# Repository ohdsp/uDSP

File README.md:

# [Open Hardware DSP Platform](www.ohdsp.org)
## uDSP 1.1
### A 5cm x 5cm DSP board using Analog Device SigmaDSP devices
### Supports ADAU1466, ADAU1462, ADAU1452, ADAU1451, ADAU1450
### Selfboot and external control supported
### All I/O routed out
---
# README
### Disclaimer
Copyright Paul Janicki 2019

Licensed under the TAPR Open Hardware License (www.tapr.org/OHL)

This documentation is distributed WITHOUT ANY EXPRESS OR IMPLIED WARRANTY, INCLUDING OF MERCHANTABILITY, SATISFACTORY QUALITY AND FITNESS FOR A PARTICULAR PURPOSE.

### Changelog
1.1:
Add CS1 and CS2 to SPI header - removed 3V3 power
Add 3V3 monitor option to reset circuit

### What is this repository for?

**Quick summary**

This is a simple self-bootable DSP board with 4 I2S input and 4 I2S output connectors. When used with the ADAU146x, ADAU1451 and ADAU1452 parts there are also optical input and output connectors for off-board mounted connectors. 

There is an SPI connector for connection to the Analog Devices SigmaStudio USBi to EZ-Board Adapter (ADZS-USBI2EZB) or equivalent. 

The board also features master and slave SPI connectors for use with other boards. 

The board has space for a self-boot EEPROM. When used with the ADZS-USBI2EZB or compatible device the board can be programmed to selfboot with the last program written. The board can also be controlled using an external mircocontroller.

This board forms part the of the open hardware DSP platform which is designed to be a highly customisable and flexible DSP platform. 

This repository contains the KiCad design files, manufacturing Gerber/drill files, and PDF/drawing files for this board.

### What is the project folder structure?
Most folder names are self explanatory. Starting from the top level:
*uDSP*
+ *Bill of Materials*  - This contains the bill of materials in CVS, LibreOffice Calc and XML formats
+ *Drawings* - This contains PDF and SVG Schematic and PCB files
+ *Gerbers* - This contains the PCB Gerbers and drill drawings for manufacture, there is also a zip file ready to send to most manufacturers
+ *KiCad* - This contains the original KiCad schematic and PCB design files

### How do I get set up?

**Summary of set up**

1. Set your self up a directory on a local disk, something simple will make life easier (eg C:\Electronics on Windows as used here), but anywhere will do just fine.
2. Download the Kicad-Libs from [https://github.com/ohdsp/KiCad-Libs](https://github.com/ohdsp/KiCad-Libs) and place in C:\Electronics\Kicad-Libs (or your chosen folder) 
3. Create a OHDSP subdirectory in C:\Electronics (so C:\Electronics\OHDSP)
3. Download this project to C:\Electronics\OHDSP\uDSP
4. Fire up Kicad
5. Open the main project file C:\Electronics\OHDSP\uDSP\KiCad\uDSP.pro
7. Do as you wish with the project, just keep it under the TAPR Open Hardware License.
Note: For library issues see below.

Make sure your git setup doesn't exclude files used in the project (like .LIB files) or things may go wrong down the line.

**KiCad Library Configuration**

Note that libraries are setup using relative paths, if you follow the above instructions things should work just fine. Below is the default library setup.

To setup eeschema component libraries:
From KiCad main window go to menu Tools -> Edit Schematic Symbols. In the new Window go to menu Preferences -> Manage Symbol Libraries.

On the new "Symbol Libraries" window select the "Project Specific Libraries" tab. The "Append Library" and "Remove Library" buttons can be used to add/remove enteries.
The standard setup is:

|   | Active | Nickname        | Library Path                                        | Plugin Type | Options | Description |
|---|--------|-----------------|-----------------------------------------------------|-------------|---------|-------------|
| 1 | Ticked | power           | ${KICAD_SYMBOL_DIR}/power.lib                       | Legacy      | (blank) | (blank)     |
| 2 | Ticked | MyKiCadLibs-Lib | ${KIPRJMOD}/../../../KiCad-Libs/MyKiCadLibs-Lib.lib | Legacy      | (blank) | (blank)     |

${KICAD_SYMBOL_DIR}  is set under the Enviromnet Variable Configuration. Close Symbol Libraries dialogue and go "Preferences" -> "Configure Paths..."

${KICAD_SYMBOL_DIR} is set to C:\Program Files\KiCad\share\kicad\library - this is the default for a KiCad install on the C drive

${KIPRJMOD} is automatically set to the location of the project (.pro file), in this example this would be C:\Electronics\OHDSP\uDSP\KiCad

To setup Pcbnew libraries:
From KiCad main window go to menu Tools -> Edit PCB Footprints. In the new Window go to menu Preferences -> Manage Symbol Libraries.

On the new "Symbol Libraries" window select the "Project Specific Libraries" tab. The "Append Library" and "Remove Library" buttons can be used to add/remove enteries.
The standard setup is:

|   | Active | Nickname               | Library Path                                                  | Plugin Type | Options | Description |
|---|--------|------------------------|---------------------------------------------------------------|-------------|---------|-------------|
| 1 | Ticked | MyKiCadLibs-Footprints | ${KIPRJMOD}/../../../KiCad-Libs/MyKiCadLibs-Footprints.pretty | KiCad       | (blank) | (blank)     |

${KIPRJMOD} is automatically set to the location of the project (.pro file), in this example this would be C:\Electronics\OHDSP\uDSP\KiCad

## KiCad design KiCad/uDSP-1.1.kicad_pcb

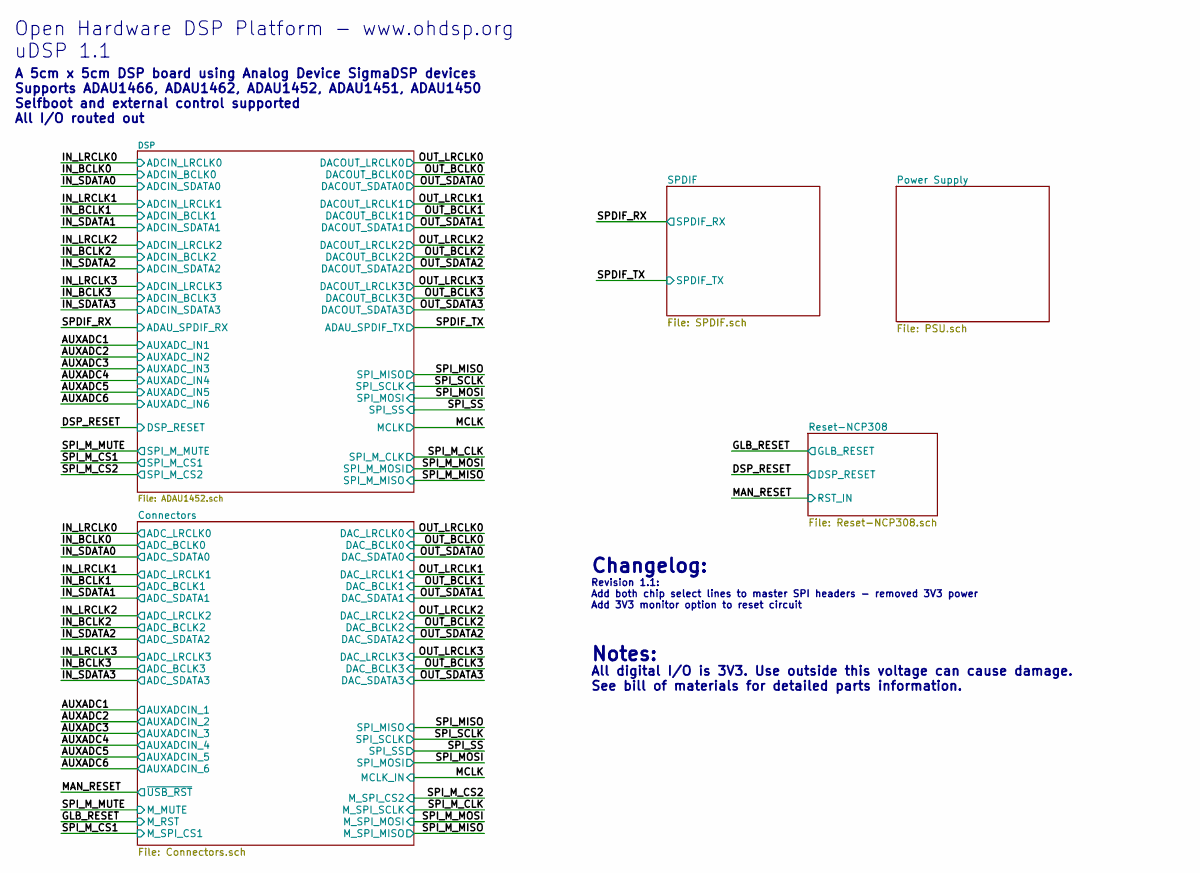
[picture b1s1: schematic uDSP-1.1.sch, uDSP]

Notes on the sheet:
All digital I/O is 3V3. Use outside this voltage can cause damage. See bill of materials for detailed parts information.
Notes:
A 5cm x 5cm DSP board using Analog Device SigmaDSP devices Supports ADAU1466, ADAU1462, ADAU1452, ADAU1451, ADAU1450 Selfboot and external control supported All I/O routed out
Open Hardware DSP Platform - www.ohdsp.org uDSP 1.1
Changelog:
Revision 1.1: Add both chip select lines to master SPI headers - removed 3V3 power Add 3V3 monitor option to reset circuit

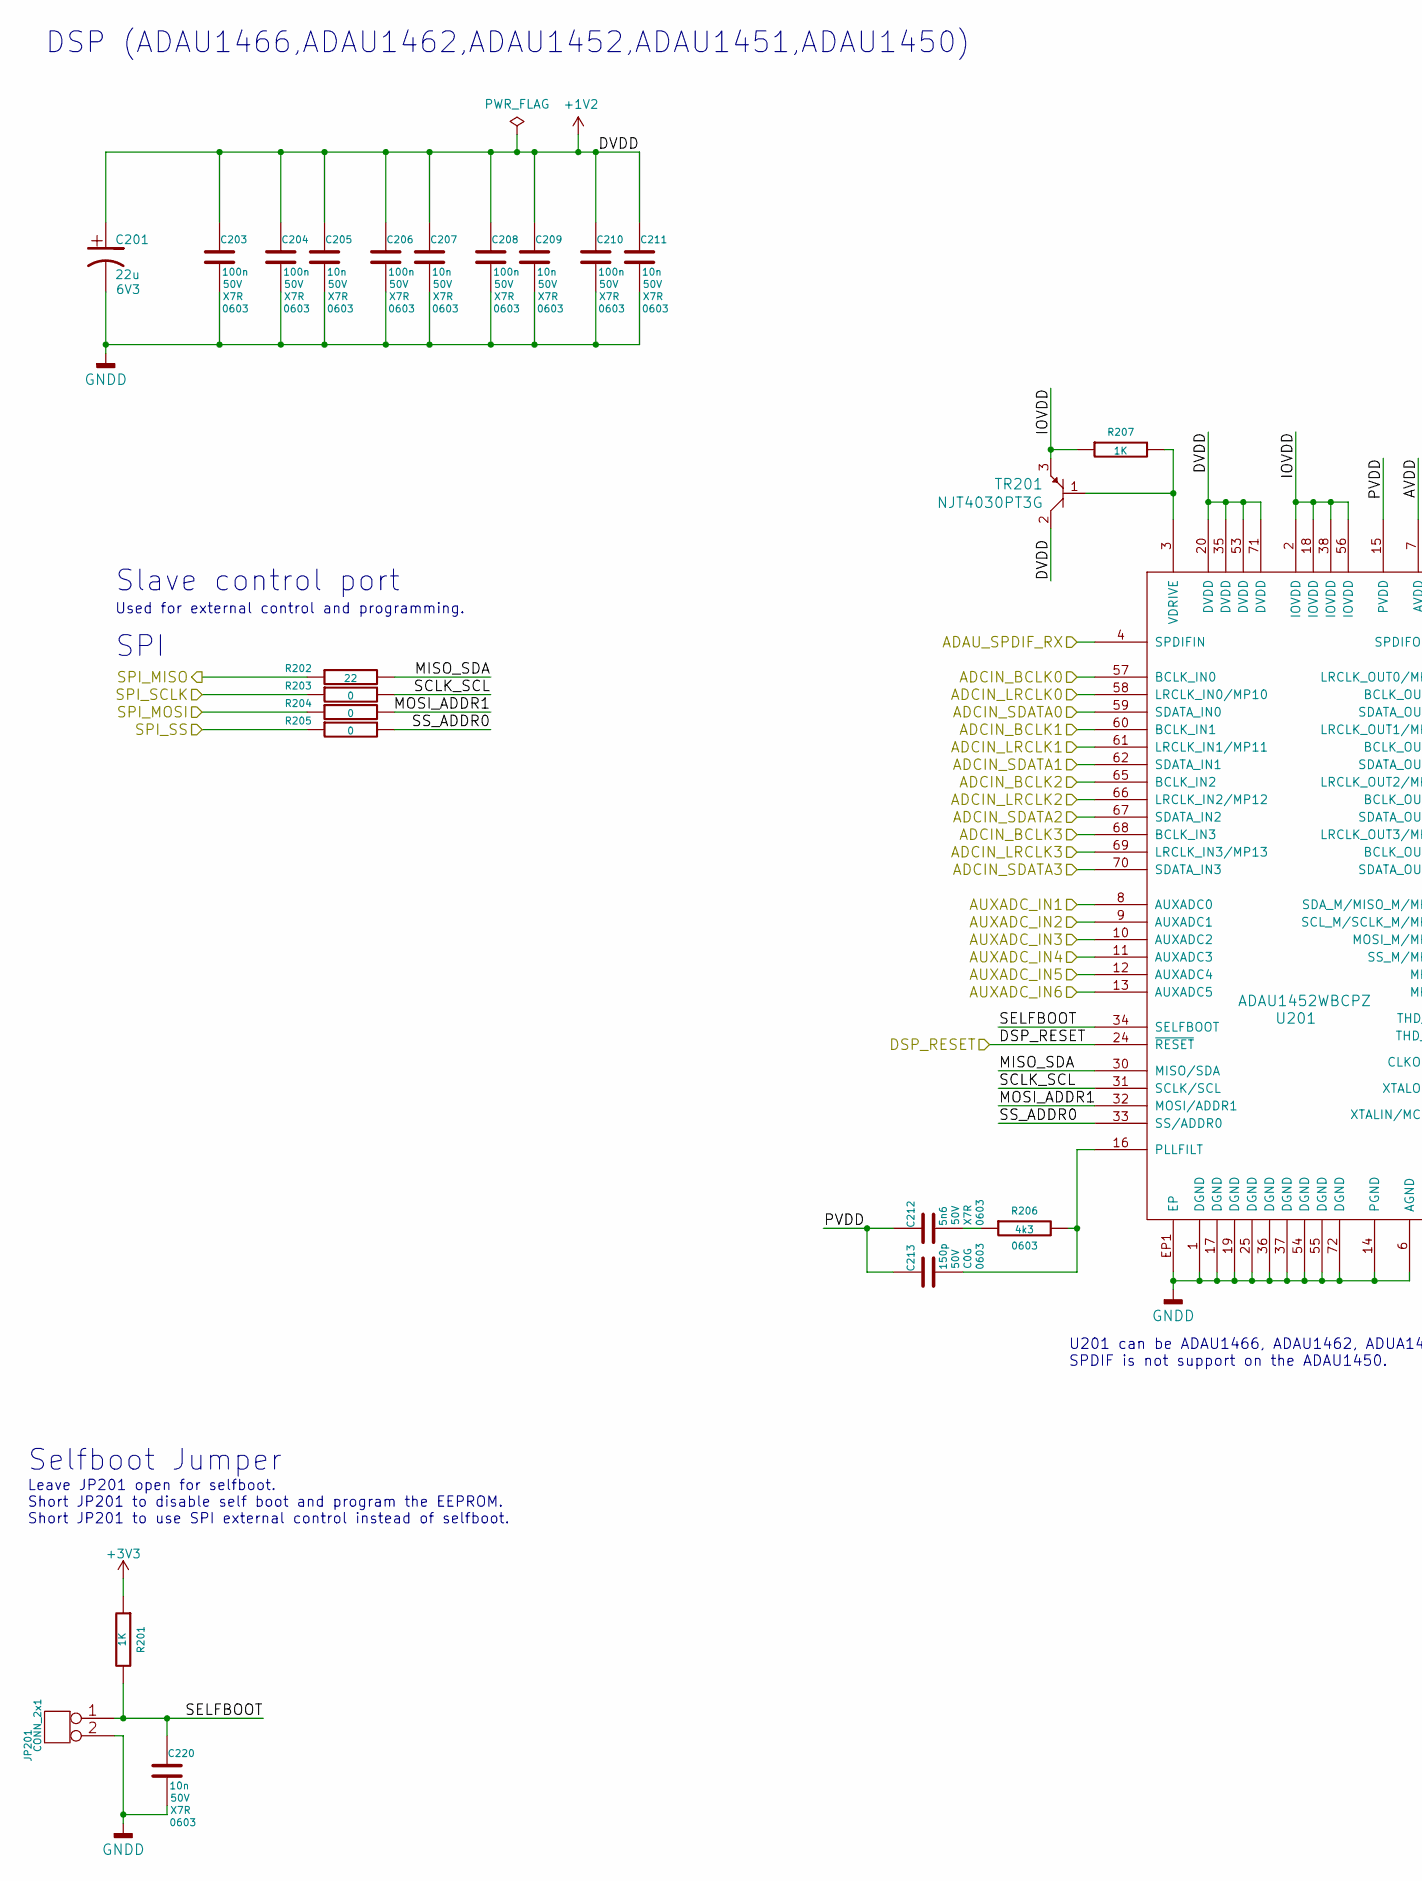
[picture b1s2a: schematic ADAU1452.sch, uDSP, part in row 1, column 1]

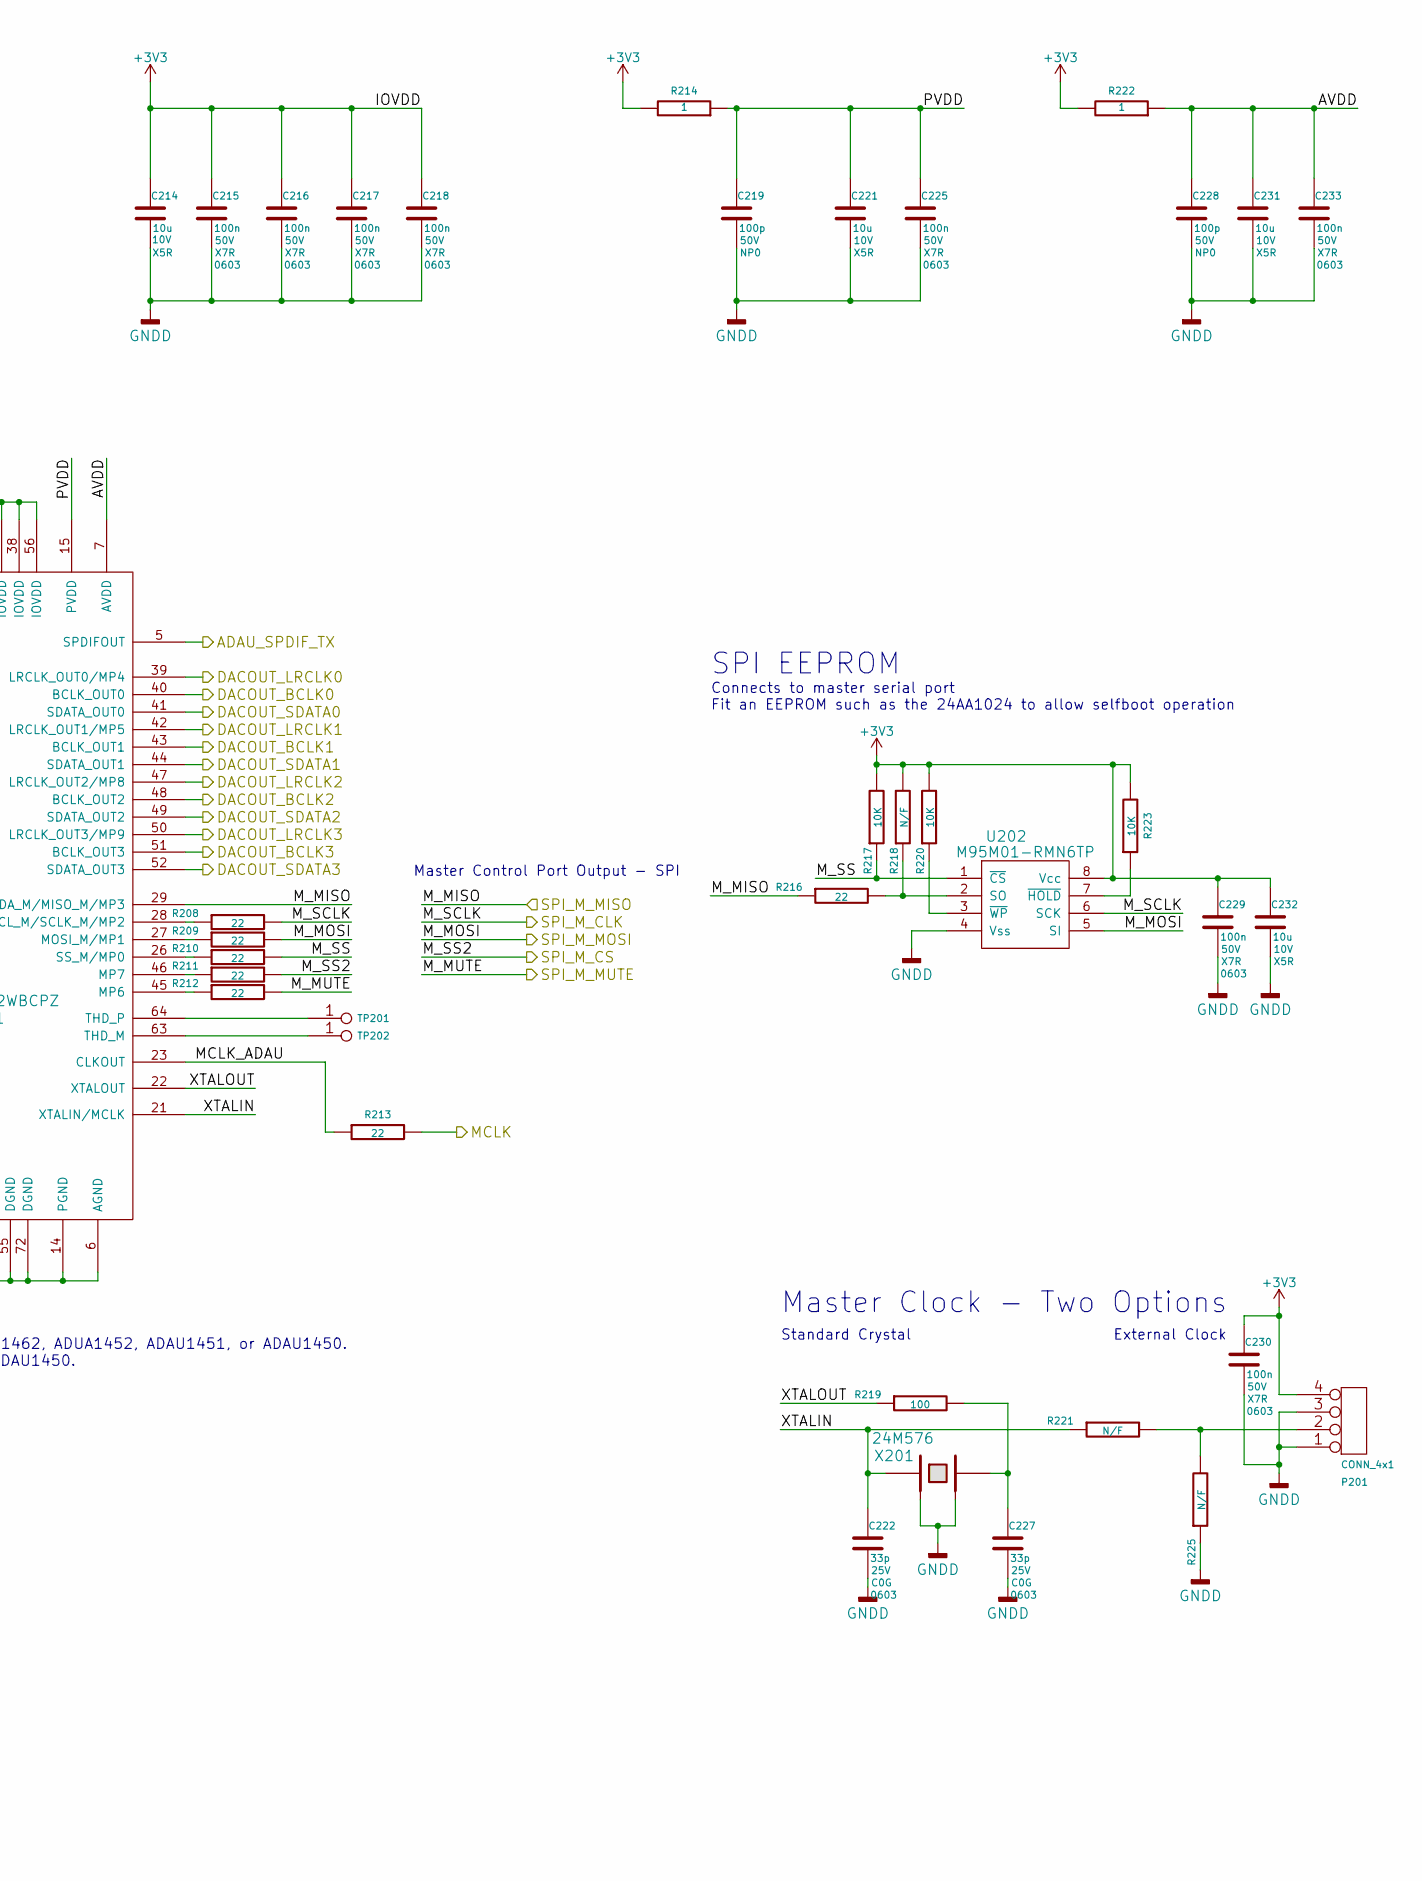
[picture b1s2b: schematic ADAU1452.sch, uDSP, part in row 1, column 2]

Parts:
C201: 22u; CAP-SMD-SIZE-B; Voltage 6V3
C203, C204, C206, C208, C210, C215, C216, C217, C218, C225, C229, C230, C233: 100n; SMD-0603; Voltage 50V; Tolerance 10%
C205, C207, C209, C211, C220: 10n; SMD-0603; Voltage 50V; Tolerance 10%
C212: 5n6; SMD-0603; Voltage 50V; Tolerance 10%
C213: 150p; SMD-0603; Voltage 50V; Tolerance 5%
C214: 10u; SMD-0805; Voltage 10V; Tolerance 20%
C219, C228: 100p; SMD-0603; Voltage 50V; Tolerance 5%
C221, C231, C232: 10u; SMD-0603; Voltage 10V; Tolerance 10%
C222, C227: 33p; SMD-0603; Voltage 25V; Tolerance 5%
JP201: CONN_2x1; CONN_SIL_2_1MM
P201: CONN_4x1; CONN_SIL_4_1MM
R201, R207: 1K; SMD-0603; Tolerance 1%
R202, R208, R209, R210, R211, R212, R213, R216: 22; SMD-0603; Tolerance 1%
R203, R204, R205: 0; SMD-0603; Tolerance 1%
R206: 4k3; SMD-0603; Tolerance 1%
R214, R222: 1; SMD-0603; Tolerance 1%
R217, R220, R223: 10K; SMD-0603; Tolerance 1%
R218, R221, R225: N/F; SMD-0603; Tolerance 1%
R219: 100; SMD-0603; Tolerance 1%
TP201, TP202: PIN; TP-1mm
TR201: NJT4030PT3G; IC-SOT-223
U201: ADAU1452WBCPZ; IC-LFCSP72-HANDFIT
U202: M95M01-RMN6TP; IC_SOIC_8
X201: 24M576; XTAL_3.2x2.5_4PIN

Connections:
+1V2: C201.1, C203.1, C204.1, C205.1, C206.1, C207.1, C208.1, C209.1, C210.1, C211.1, TR201.2, U201.20 (DVDD), U201.35 (DVDD), U201.53 (DVDD), U201.71 (DVDD); also elsewhere on the board
/AUXADC1: U201.8 (AUXADC0); also elsewhere on the board
/AUXADC2: U201.9 (AUXADC1); also elsewhere on the board
/AUXADC3: U201.10 (AUXADC2); also elsewhere on the board
/AUXADC4: U201.11 (AUXADC3); also elsewhere on the board
/AUXADC5: U201.12 (AUXADC4); also elsewhere on the board
/AUXADC6: U201.13 (AUXADC5); also elsewhere on the board
/DSP/AVDD: C228.1, C231.1, C233.1, R222.1, U201.7 (AVDD)
/DSP/MCLK_ADAU: R213.1, U201.23 (CLKOUT)
/DSP/MISO_SDA: R202.2, U201.30 (MISO/SDA)
/DSP/MOSI_ADDR1: R204.2, U201.32 (MOSI/ADDR1)
/DSP/PVDD: C212.1, C213.1, C219.1, C221.1, C225.1, R214.1, U201.15 (PVDD)
/DSP/SCLK_SCL: R203.2, U201.31 (SCLK/SCL)
/DSP/SELFBOOT: C220.1, JP201.1, R201.2, U201.34 (SELFBOOT)
/DSP/SS_ADDR0: R205.2, U201.33 (SS/ADDR0)
/DSP/XTALIN: C222.1, R221.1, U201.21 (XTALIN/MCLK), X201.1
/DSP/XTALOUT: R219.1, U201.22 (XTALOUT)
/DSP_RESET: U201.24 (~RESET); also elsewhere on the board
/IN_BCLK0: U201.57 (BCLK_IN0); also elsewhere on the board
/IN_BCLK1: U201.60 (BCLK_IN1); also elsewhere on the board
/IN_BCLK2: U201.65 (BCLK_IN2); also elsewhere on the board
/IN_BCLK3: U201.68 (BCLK_IN3); also elsewhere on the board
/IN_LRCLK0: U201.58 (LRCLK_IN0/MP10); also elsewhere on the board
/IN_LRCLK1: U201.61 (LRCLK_IN1/MP11); also elsewhere on the board
/IN_LRCLK2: U201.66 (LRCLK_IN2/MP12); also elsewhere on the board
/IN_LRCLK3: U201.69 (LRCLK_IN3/MP13); also elsewhere on the board
/IN_SDATA0: U201.59 (SDATA_IN0); also elsewhere on the board
/IN_SDATA1: U201.62 (SDATA_IN1); also elsewhere on the board
/IN_SDATA2: U201.67 (SDATA_IN2); also elsewhere on the board
/IN_SDATA3: U201.70 (SDATA_IN3); also elsewhere on the board
/MCLK: R213.2; also elsewhere on the board
/OUT_BCLK0: U201.40 (BCLK_OUT0); also elsewhere on the board
/OUT_BCLK1: U201.43 (BCLK_OUT1); also elsewhere on the board
/OUT_BCLK2: U201.48 (BCLK_OUT2); also elsewhere on the board
/OUT_BCLK3: U201.51 (BCLK_OUT3); also elsewhere on the board
/OUT_LRCLK0: U201.39 (LRCLK_OUT0/MP4); also elsewhere on the board
/OUT_LRCLK1: U201.42 (LRCLK_OUT1/MP5); also elsewhere on the board
/OUT_LRCLK2: U201.47 (LRCLK_OUT2/MP8); also elsewhere on the board
/OUT_LRCLK3: U201.50 (LRCLK_OUT3/MP9); also elsewhere on the board
/OUT_SDATA0: U201.41 (SDATA_OUT0); also elsewhere on the board
/OUT_SDATA1: U201.44 (SDATA_OUT1); also elsewhere on the board
/OUT_SDATA2: U201.49 (SDATA_OUT2); also elsewhere on the board
/OUT_SDATA3: U201.52 (SDATA_OUT3); also elsewhere on the board
/SPDIF_RX: U201.4 (SPDIFIN); also elsewhere on the board
/SPDIF_TX: U201.5 (SPDIFOUT); also elsewhere on the board
/SPI_MISO: R202.1; also elsewhere on the board
/SPI_MOSI: R204.1; also elsewhere on the board
/SPI_M_CLK: R208.2, U202.6 (SCK); also elsewhere on the board
/SPI_M_CS2: R211.2; also elsewhere on the board
/SPI_M_MISO: R216.1, U201.29 (SDA_M/MISO_M/MP3); also elsewhere on the board
/SPI_M_MOSI: R209.2, U202.5 (SI); also elsewhere on the board
/SPI_M_MUTE: R212.2; also elsewhere on the board
/SPI_SCLK: R203.1; also elsewhere on the board
/SPI_SS: R205.1; also elsewhere on the board
GNDD: C201.2, C203.2, C204.2, C205.2, C206.2, C207.2, C208.2, C209.2, C210.2, C211.2, C214.2, C215.2, C216.2, C217.2, C218.2, C219.2, C220.2, C221.2, C222.2, C225.2, C227.2, C228.2, C229.2, C230.2, C231.2, C232.2, C233.2, JP201.2, P201.1, P201.3, R225.1, U201.1 (DGND), U201.6 (AGND), U201.14 (PGND), U201.17 (DGND), U201.19 (DGND), U201.25 (DGND), U201.36 (DGND), U201.37 (DGND), U201.54 (DGND), U201.55 (DGND), U201.72 (DGND), U201.EP1 (EP), U202.4 (Vss), X201.2, X201.4; also elsewhere on the board
unnamed: C212.2, R206.1
unnamed: C213.2, R206.2, U201.16 (PLLFILT)
unnamed: C227.1, R219.2, X201.3
unnamed: P201.2, R221.2, R225.2
unnamed: R207.2, TR201.1, U201.3 (VDRIVE)
unnamed: R208.1, U201.28 (SCL_M/SCLK_M/MP2)
unnamed: R209.1, U201.27 (MOSI_M/MP1)
unnamed: R210.1, U201.26 (SS_M/MP0)
unnamed: R211.1, U201.46 (MP7)
unnamed: R212.1, U201.45 (MP6)
unnamed: R216.2, R218.1, U202.2 (SO)
unnamed: R220.1, U202.3 (~WP)
unnamed: R223.1, U202.7 (~HOLD)
unnamed: TP201.1, U201.64 (THD_P)
unnamed: TP202.1, U201.63 (THD_M)

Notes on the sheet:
Selfboot Jumper
Leave JP201 open for selfboot. Short JP201 to disable self boot and program the EEPROM. Short JP201 to use SPI external control instead of selfboot.
SPI EEPROM
Master Clock - Two Options
Standard Crystal
Connects to master serial port Fit an EEPROM such as the 24AA1024 to allow selfboot operation
Slave control port
Used for external control and programming.
External Clock
SPI
Master Control Port Output - SPI
U201 can be ADAU1466, ADAU1462, ADUA1452, ADAU1451, or ADAU1450. SPDIF is not support on the ADAU1450.
DSP (ADAU1466,ADAU1462,ADAU1452,ADAU1451,ADAU1450)

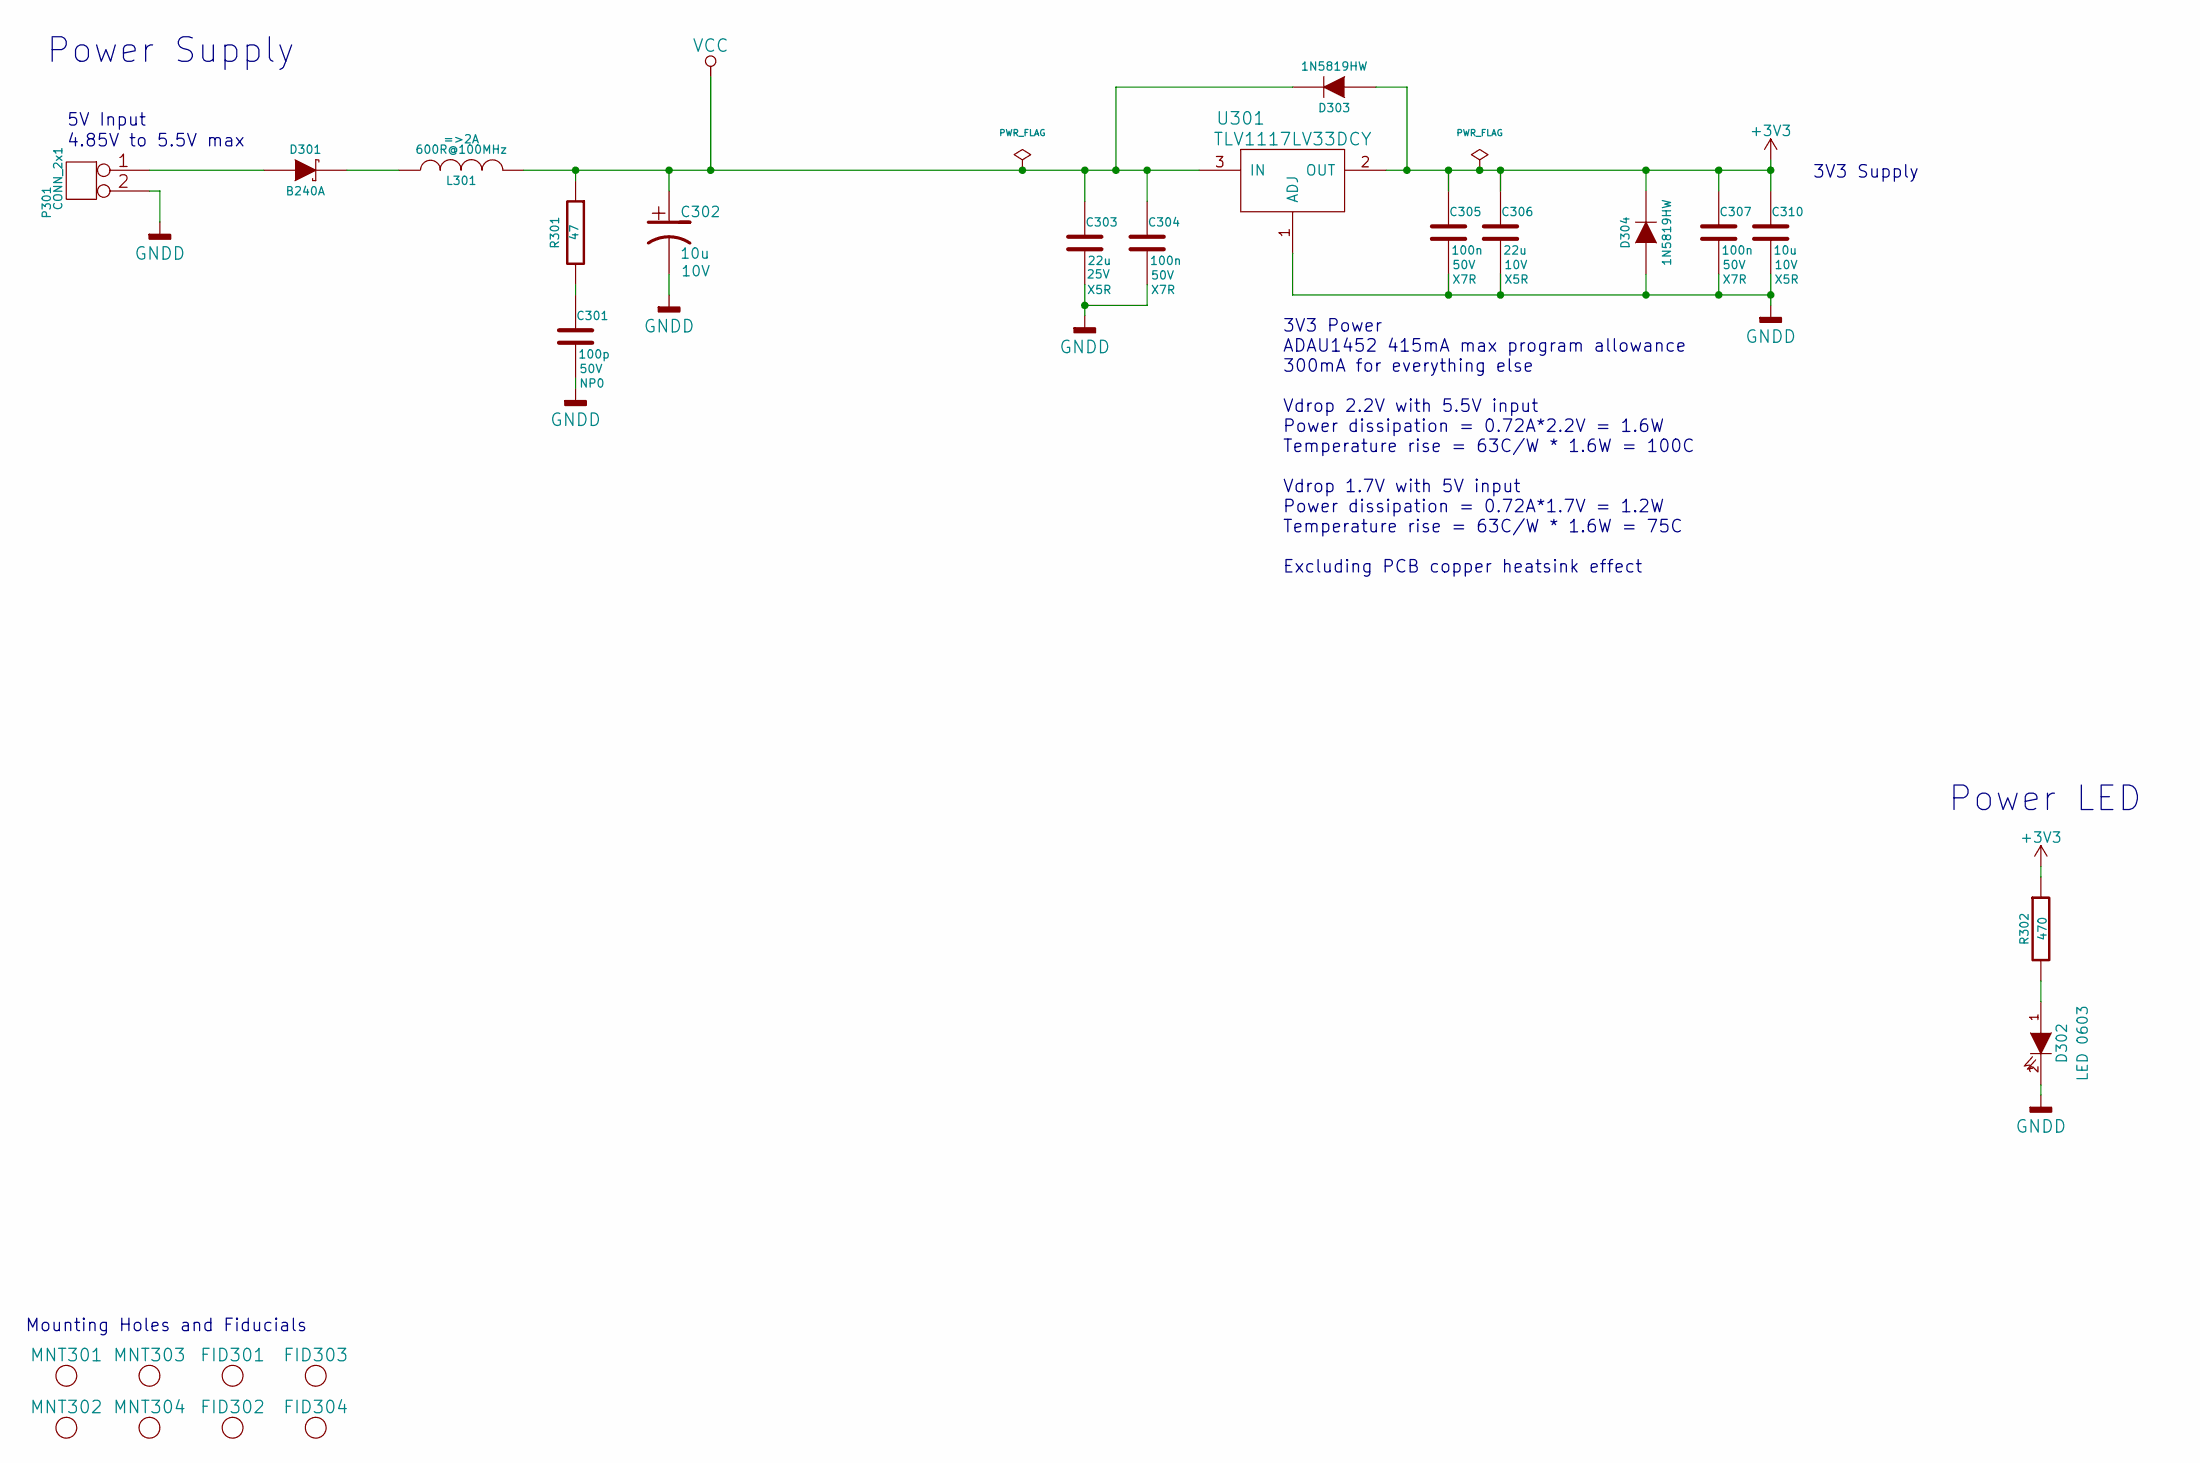
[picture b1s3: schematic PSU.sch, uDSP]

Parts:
C301: 100p; SMD-0603; Voltage 50V; Tolerance 5%
C302: 10u; CAP-SMD-SIZE-B; Voltage 10V
C303: 22u; SMD-0805; Voltage 25V; Tolerance 20%
C304, C305, C307: 100n; SMD-0603; Voltage 50V; Tolerance 10%
C306: 22u; SMD-0603; Voltage 10V; Tolerance 20%
C310: 10u; SMD-0603; Voltage 10V; Tolerance 20%
D301: B240A; DIODE-SMA
D302: LED 0603; SMD-0603-LED
D303, D304: 1N5819HW; DIODE-SOD-123
FID301, FID302, FID303, FID304: MNT_HOLE; FID-1MM-3MM
L301: 600R@100MHz; SMD-0805
MNT301, MNT302, MNT303, MNT304: MNT_HOLE; MNT_HOLE_3.2mm
P301: CONN_2x1; CONN-2WAY-2.54mm-3.81mm-SPACING
R301: 47; SMD-0603; Tolerance 1%
R302: 470; SMD-0603; Tolerance 1%
U301: TLV1117LV33DCY; IC-SOT-223

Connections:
GNDD: C301.2, C302.2, C303.2, C304.2, C305.2, C306.2, C307.2, C310.2, D302.2 (K), D304.1 (A), P301.2, U301.1 (ADJ); also elsewhere on the board
unnamed: C301.1, R301.2
unnamed: D301.1 (A), P301.1
unnamed: D301.2 (K), L301.1
unnamed: D302.1 (A), R302.2
VCC: C302.1, C303.1, C304.1, D303.2 (K), L301.2, R301.1, U301.3 (IN)

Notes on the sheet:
Power Supply
5V Input
3V3 Supply
Mounting Holes and Fiducials
3V3 Power ADAU1452 415mA max program allowance 300mA for everything else Vdrop 2.2V with 5.5V input Power dissipation = 0.72A*2.2V = 1.6W Temperature rise = 63C/W * 1.6W = 100C Vdrop 1.7V with 5V input Power dissipation = 0.72A*1.7V = 1.2W Temperature rise = 63C/W * 1.6W = 75C Excluding PCB copper 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
4.85V to 5.5V max
Power LED

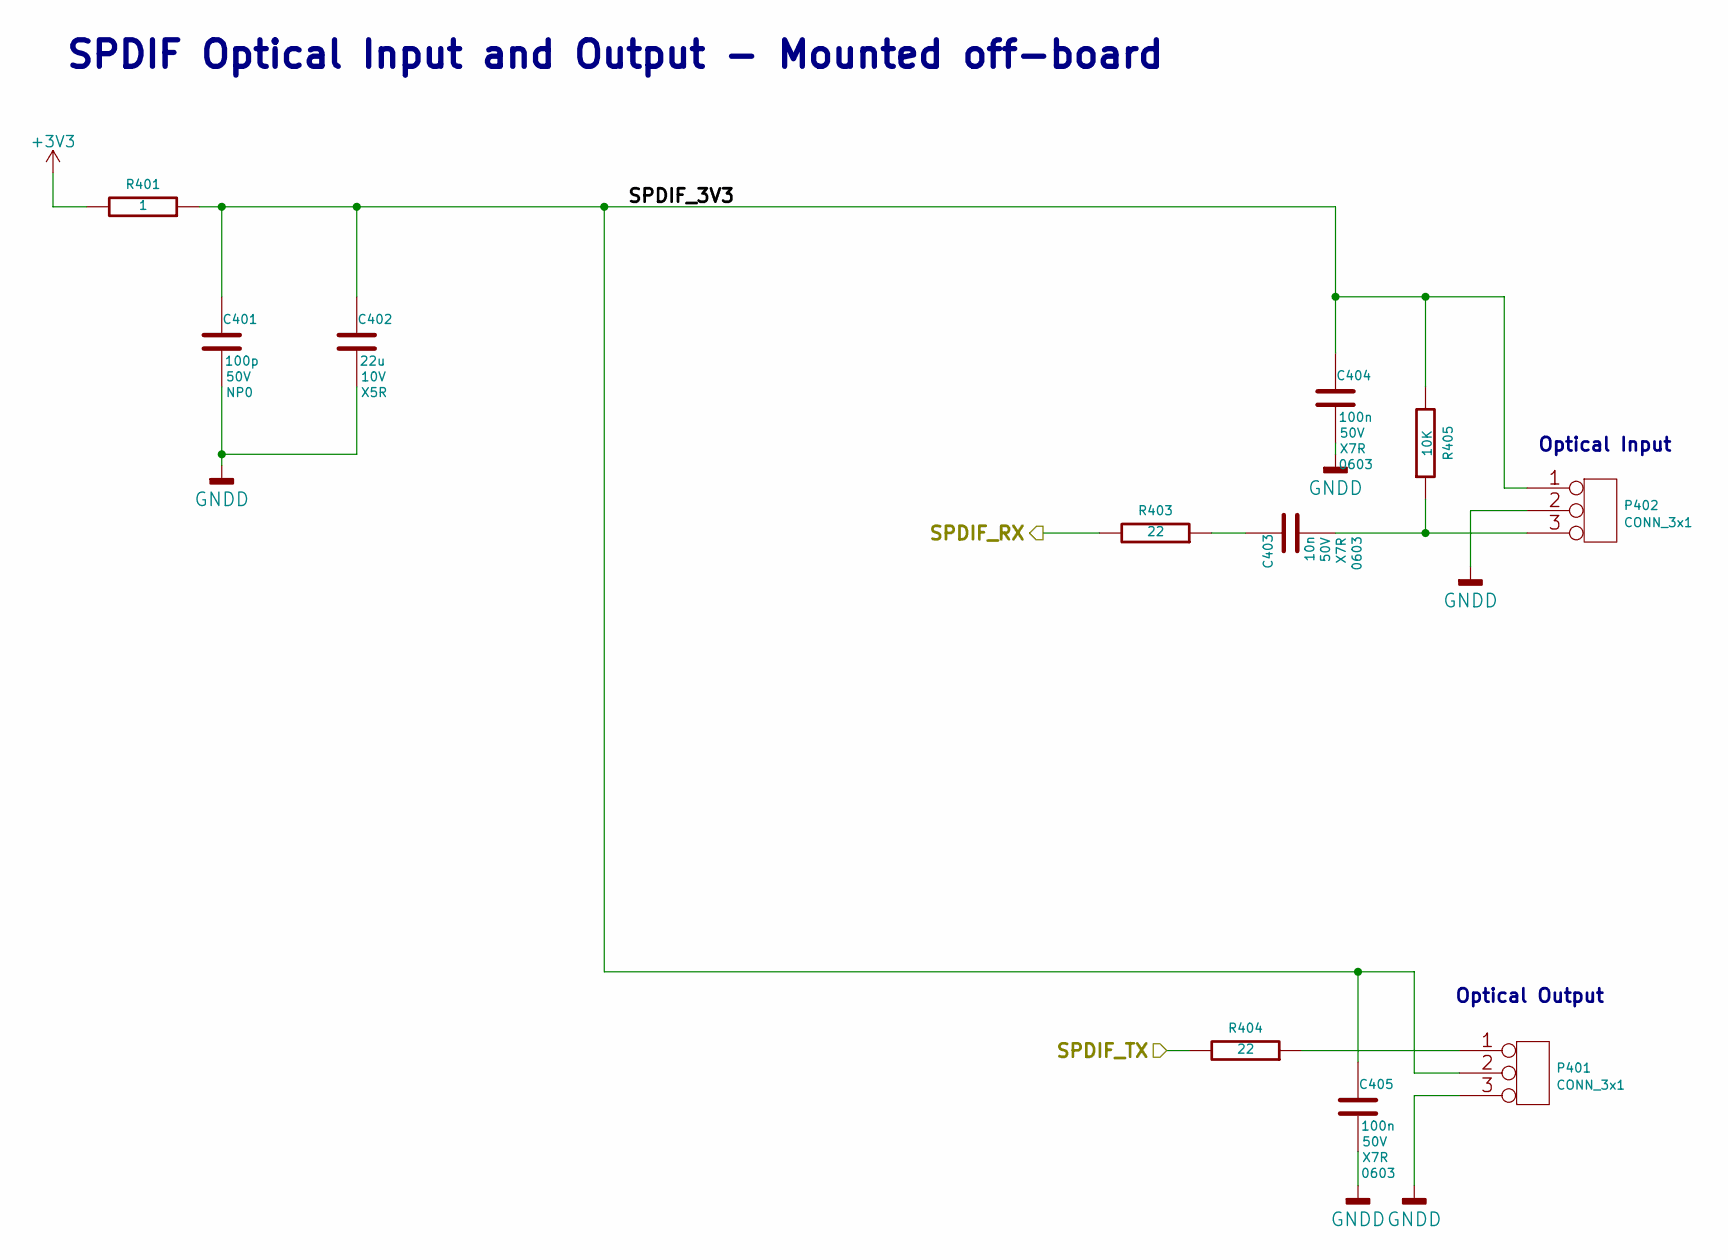
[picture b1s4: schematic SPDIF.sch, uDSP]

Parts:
C401: 100p; SMD-0603; Voltage 50V; Tolerance 5%
C402: 22u; SMD-0603; Voltage 10V; Tolerance 10%
C403: 10n; SMD-0603; Voltage 50V; Tolerance 10%
C404, C405: 100n; SMD-0603; Voltage 50V; Tolerance 10%
P401, P402: CONN_3x1; CONN_SIL_3_1MM
R401: 1; SMD-0603; Tolerance 1%
R403, R404: 22; SMD-0603; Tolerance 1%
R405: 10K; SMD-0603; Tolerance 1%

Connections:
/SPDIF/SPDIF_3V3: C401.1, C402.1, C404.1, C405.1, P401.2, P402.1, R401.1, R405.2
/SPDIF_RX: R403.2; also elsewhere on the board
/SPDIF_TX: R404.2; also elsewhere on the board
GNDD: C401.2, C402.2, C404.2, C405.2, P401.3, P402.2; also elsewhere on the board
unnamed: C403.1, R403.1
unnamed: C403.2, P402.3, R405.1
unnamed: P401.1, R404.1

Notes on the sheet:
SPDIF Optical Input and Output - Mounted off-board
Optical Input
Optical Output

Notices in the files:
KiCad/uDSP-1.1.kicad_pcb:
Copyright © Paul Janicki 2019
